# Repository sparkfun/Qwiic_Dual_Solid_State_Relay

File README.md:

SparkFun Qwiic Dual Solid State Relay
========================================

[*SparkFun Qwiic Dual Solid State Relay (COM-16810)*](https://www.sparkfun.com/products/16810)

The SparkFun Qwiic Dual Solid State Relay integrates two solid state relays on to a single board allowing you to control both of them from a microcontroller via I<sup>2</sup>C with the Qwiic Ecosystem. The relays are rated for 25A @240VAC so you can control some serious power with this board. 

The Qwiic Dual Solid State Relay comes fully assembled and uses the simple [Qwiic interface](https://www.sparkfun.com/qwiic). No soldering, no voltage translation, no figuring out which pin is SDA or SCL, just plug and go!

**Note:** Controlling high voltage (110/220VAC) requires certain precautions. A beginner can do it but if you're wary of working with high voltage, you may want to consider the pre-made [IoT Power Relay](https://www.sparkfun.com/products/14236). It's not controlled via I<sup>2</sup>C but the IoT Power Relay contains shielding to prevent accidental shock.

Repository Contents
-------------------

* **/Firmware** - Latest firmware
* **/Hardware** - Eagle design files (.brd, .sch)
* **/Production** - Production panel files (.brd)

Documentation
--------------
* **[SparkFun Qwiic Relay Arduino Library](https://github.com/sparkfun/SparkFun_Qwiic_Relay_Arduino_Library)** - Arduino library for SparkFun Qwiic Relay boards.
* **[SparkFun Qwiic Relay Python Package](https://github.com/sparkfun/Qwiic_Relay_Py)** - Python package for SparkFun Qwiic Solid State Relay boards.
* **[Hookup Guide](https://learn.sparkfun.com/tutorials/sparkfun-qwiic-dual-solid-state-relay-hookup-guide)** - Basic hookup guide for the Qwiic Dual Solid State Relay.
* **[SparkFun Fritzing repo](https://github.com/sparkfun/Fritzing_Parts)** - Fritzing diagrams for SparkFun products.
* **[SparkFun 3D Model repo](https://github.com/sparkfun/3D_Models)** - 3D models of SparkFun products. 

Product Versions
----------------
* [COM-16810](https://www.sparkfun.com/products/16810)- Initial release of the Qwiic Dual Solid State Relay.

License Information
-------------------

This product is _**open source**_! 

Please review the LICENSE.md file for license information. 

If you have any questions or concerns on licensing, please contact technical support on our [SparkFun forums](https://forum.sparkfun.com/viewforum.php?f=152).

Distributed as-is; no warranty is given.

- Your friends at SparkFun.

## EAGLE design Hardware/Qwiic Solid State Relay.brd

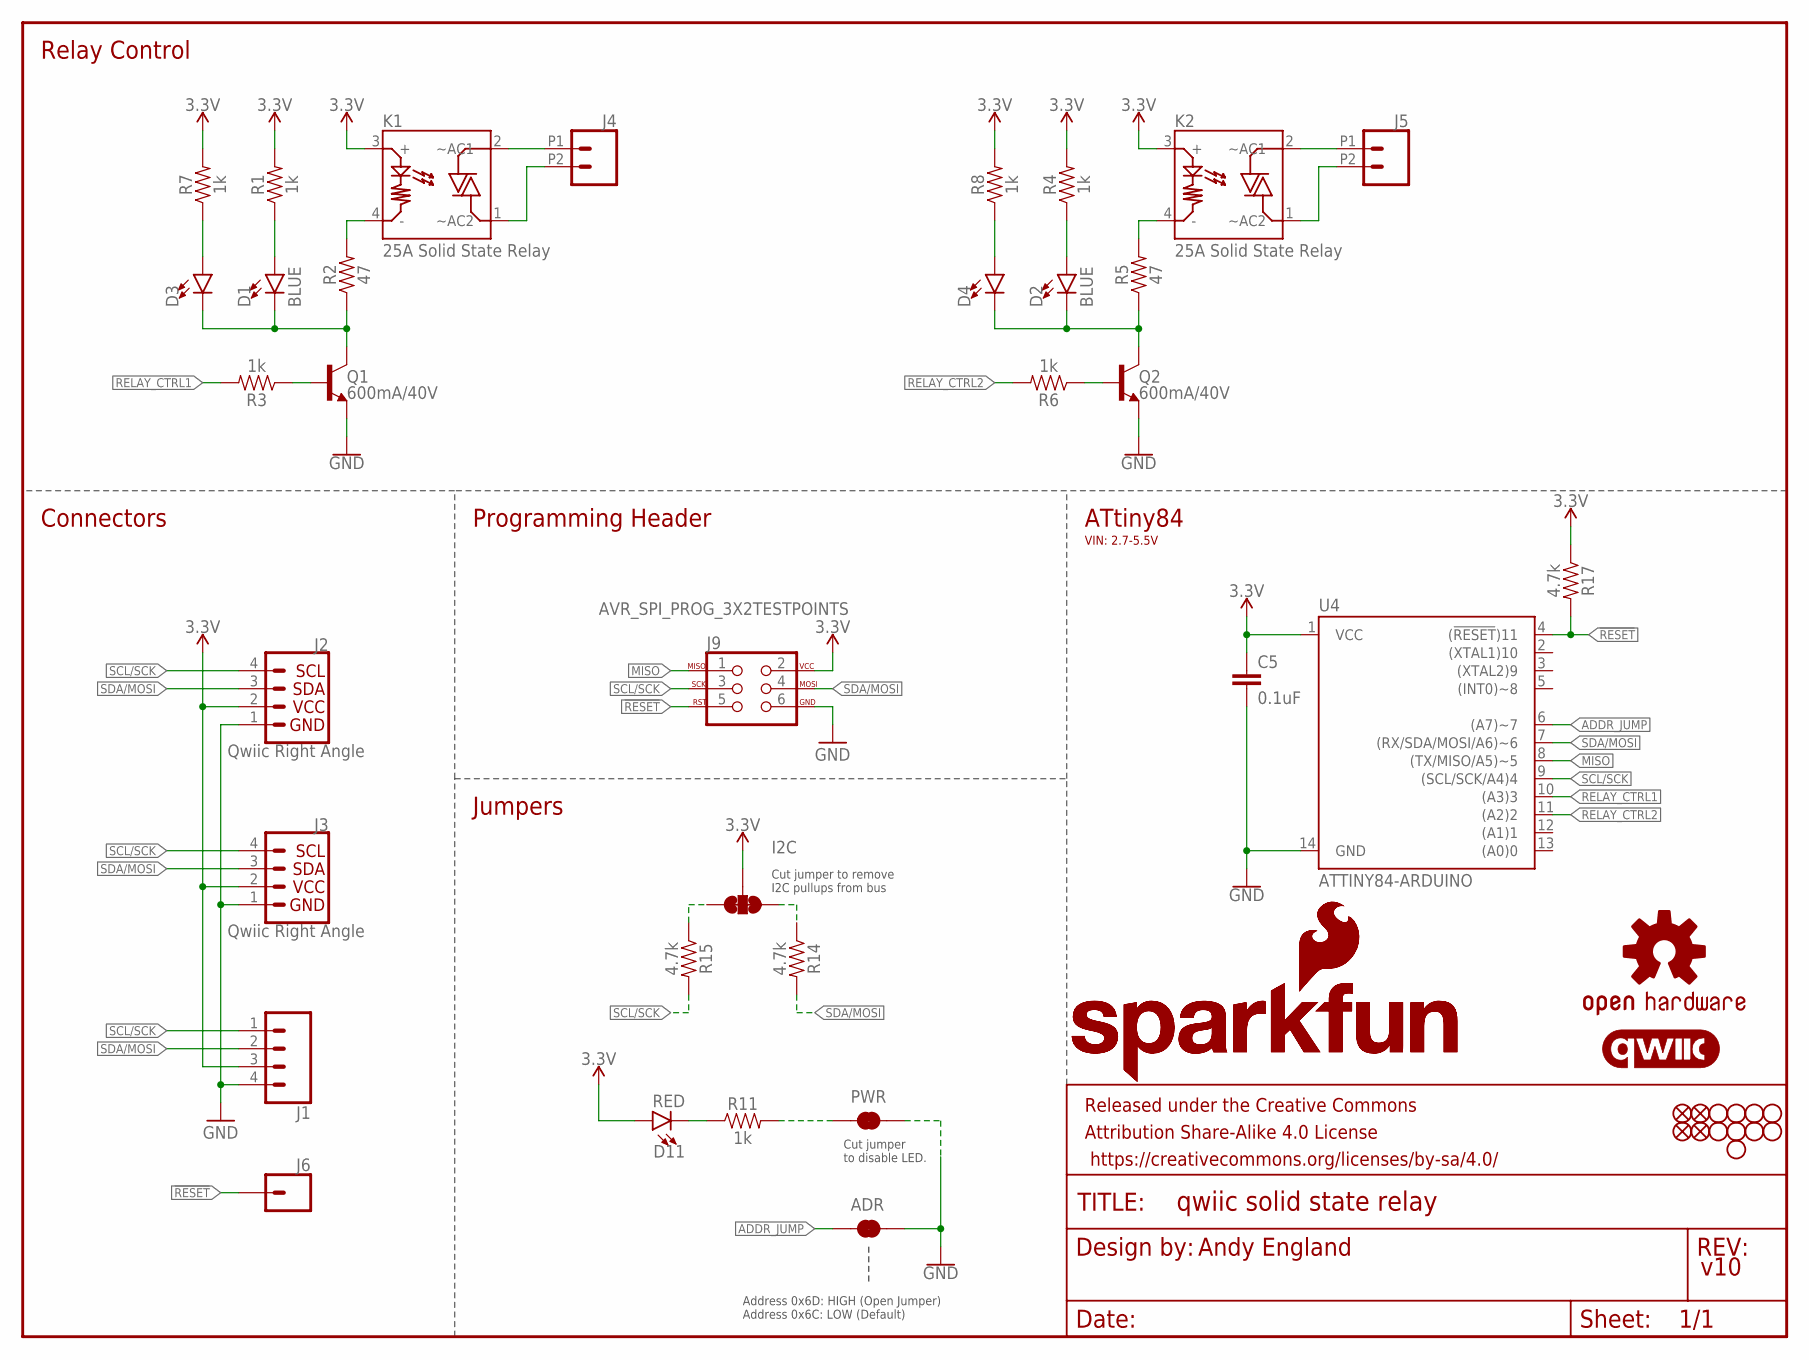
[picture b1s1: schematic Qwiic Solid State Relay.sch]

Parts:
ADR: JUMPER-SMT_2_NC_TRACE_SILK; SMT-JUMPER_2_NC_TRACE_SILK
C5: 0.1uF; 0603
D1, D2: BLUE; LED-0603
D3, D4: LED5MM; LED_5MM
D11: RED; LED-0603
FD1, FD2, FD3, FD4: FIDUCIAL1X2; FIDUCIAL-1X2
FRAME1: FRAME-LETTER; CREATIVE_COMMONS
I2C: JUMPER-SMT_3_2-NC_TRACE_SILK; SMT-JUMPER_3_2-NC_TRACE_SILK
J1: CONN_041X04_NO_SILK; 1X04_NO_SILK
J2, J3: Qwiic Right Angle; JST04_1MM_RA
J4, J5: CONN_02SCREWTERMINAL-6.35MM-2; 1X02_6.35_SCREWTERM
J6: CONN_01PTH_NO_SILK_YES_STOP; 1X01_NO_SILK
J9: AVR_SPI_PROG_3X2TESTPOINTS; 2X3_TEST_POINTS
JP1, JP2, JP3, JP4, JP5, JP6, JP7, JP8, JP10: STAND-OFF
K1, K2: 25A Solid State Relay; PTH_SOLIDSTATERELAY
LOGO1: SFE_LOGO_NAME_FLAME.2_INCH; SFE_LOGO_NAME_FLAME_.2
LOGO2: OSHW-LOGOS; OSHW-LOGO-S
LOGO3: SFE_LOGO_NAME_FLAME.3_INCH; SFE_LOGO_NAME_FLAME_.3
LOGO4: QWIIC_LOGO_5MM; QWIIC_5MM
PWR: JUMPER-SMT_2_NC_TRACE_SILK; SMT-JUMPER_2_NC_TRACE_SILK
Q1, Q2: 600mA/40V; SOT23-3
R1, R3, R4, R6, R7, R8, R11: 1k; 0603
R2, R5: 47; 0603
R14, R15, R17: 4.7k; 0603
U4: ATTINY84-ARDUINO; SO14

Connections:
3.3V: C5.1, D11.A, I2C.2, J1.3, J2.2, J3.2, J9.2, K1.3 (+), K2.3 (+), R1.2, R4.2, R7.2, R8.2, R17.1, U4.1 (VCC)
!RESET: J6.1, J9.5, R17.2, U4.4 ((!RESET!)11)
ADDR_JUMP: ADR.1, U4.6 ((A7)~7)
GND: ADR.2, C5.2, J1.4, J2.1, J3.1, J9.6, PWR.1, Q1.2 (E), Q2.2 (E), U4.14 (GND)
MISO: J9.1, U4.8 ((TX/MISO/A5)~5)
unnamed: K2.4 (-), R5.2
unnamed: D2.A, R4.1
unnamed: J4.P1 (2), K1.2 (~AC1)
unnamed: J4.P2 (1), K1.1 (~AC2)
unnamed: D1.A, R1.1
unnamed: J5.P1 (2), K2.2 (~AC1)
unnamed: J5.P2 (1), K2.1 (~AC2)
unnamed: K1.4 (-), R2.2
unnamed: D1.C, D3.K (C), Q1.3 (C), R2.1
unnamed: D3.A, R7.1
unnamed: D11.C, R11.1
unnamed: PWR.2, R11.2
unnamed: I2C.3, R15.1
unnamed: I2C.1, R14.1
unnamed: D2.C, D4.K (C), Q2.3 (C), R5.1
unnamed: D4.A, R8.1
OPTO_1: Q1.1 (B), R3.1
OPTO_2: Q2.1 (B), R6.1
RELAY_CTRL1: R3.2, U4.10 ((A3)3)
RELAY_CTRL2: R6.2, U4.11 ((A2)2)
SCL/SCK: J1.1, J2.4, J3.4, J9.3, R15.2, U4.9 ((SCL/SCK/A4)4)
SDA/MOSI: J1.2, J2.3, J3.3, J9.4, R14.2, U4.7 ((RX/SDA/MOSI/A6)~6)

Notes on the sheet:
Andy England
v10
Connectors
ATtiny84
Programming Header
Address 0x6D: HIGH (Open Jumper) Address 0x6C: LOW (Default)
Cut jumper to disable LED.
Jumpers
Relay Control
Cut jumper to remove I2C pullups from bus
VIN: 2.7-5.5V

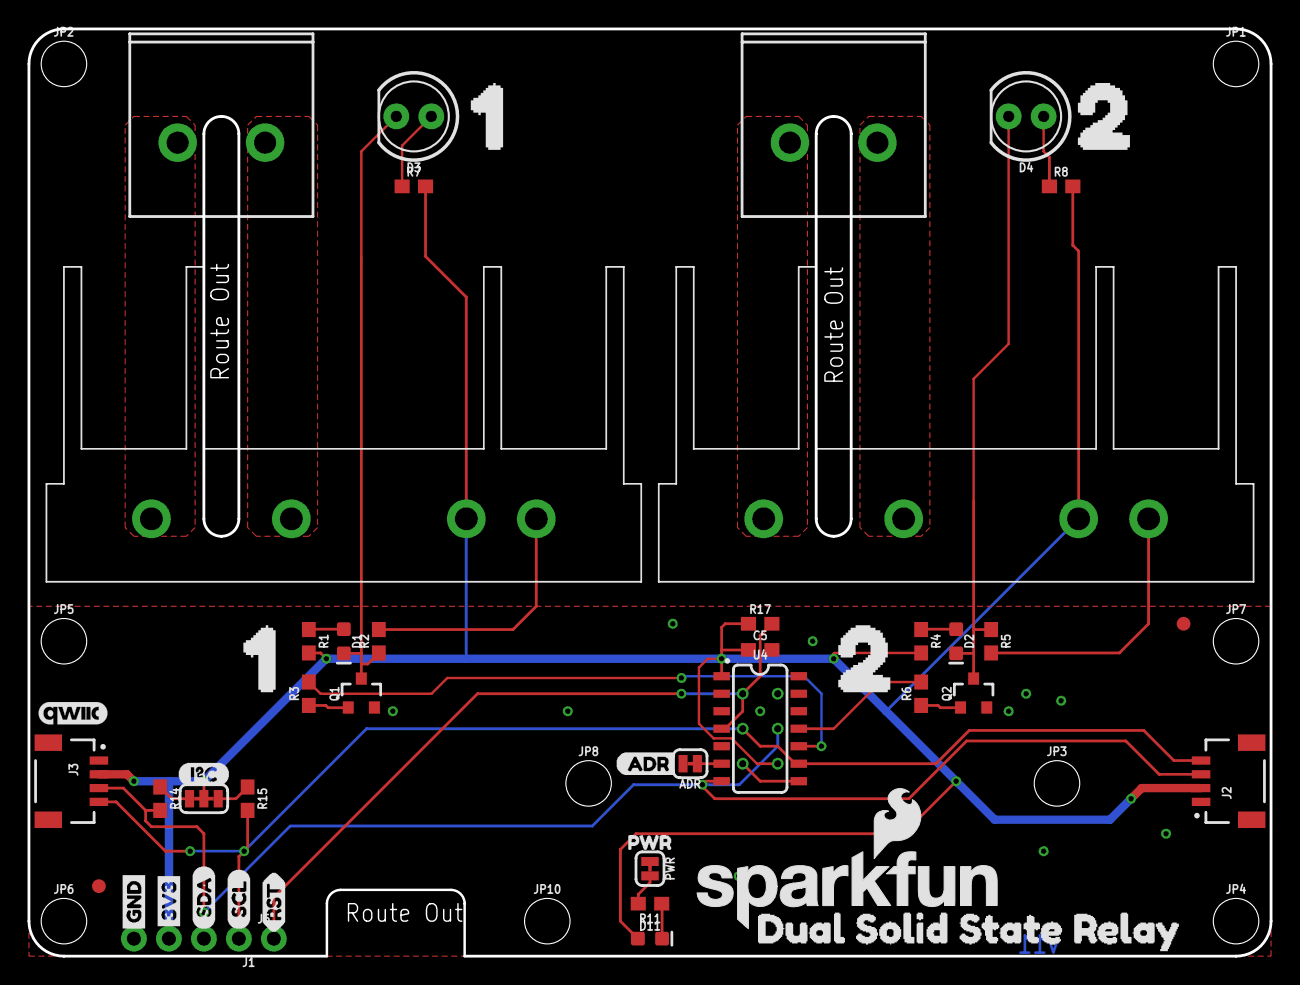
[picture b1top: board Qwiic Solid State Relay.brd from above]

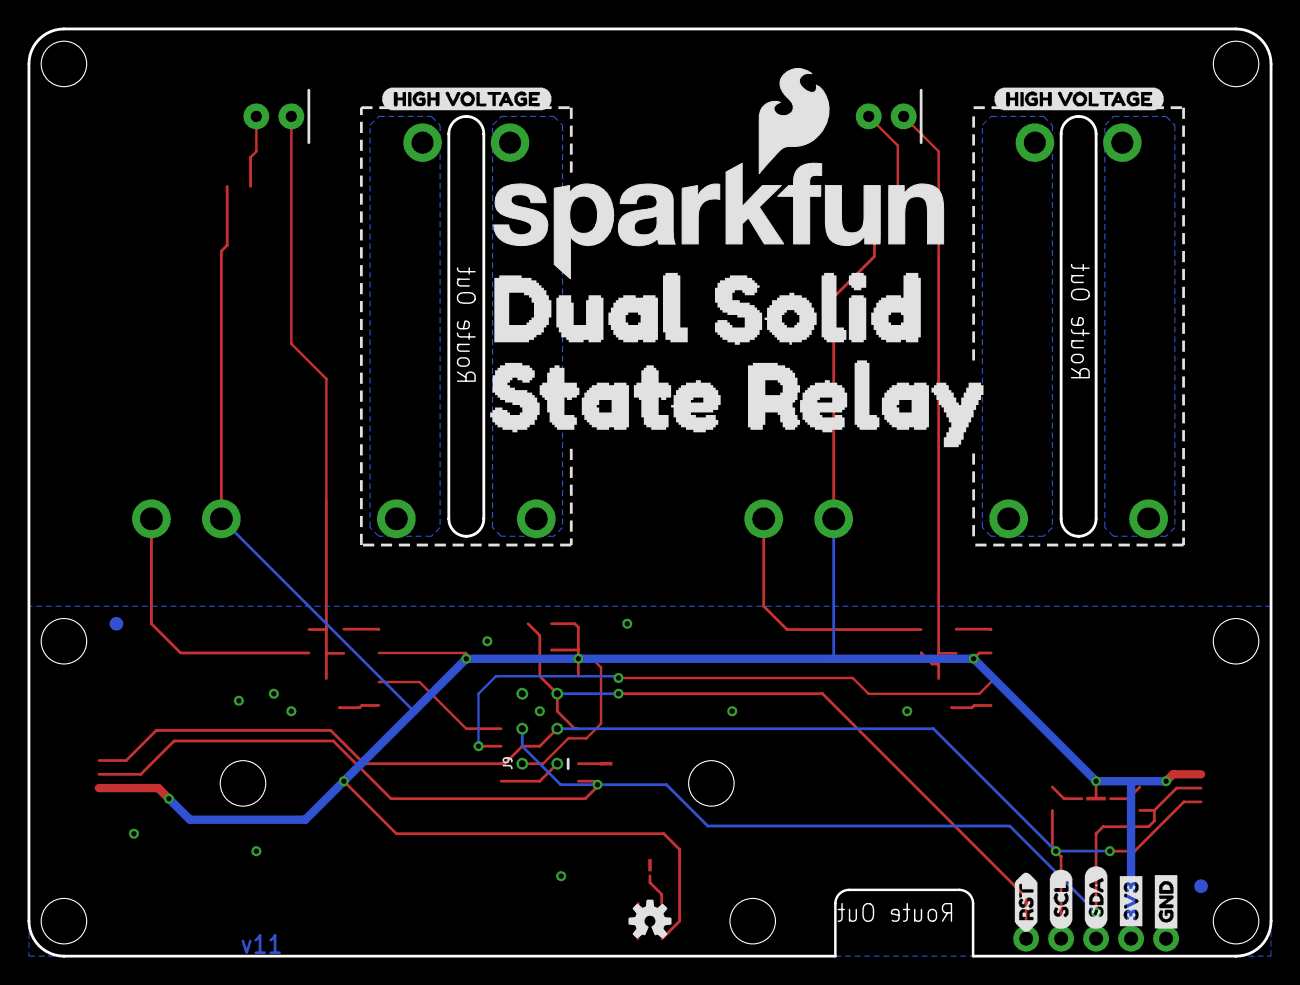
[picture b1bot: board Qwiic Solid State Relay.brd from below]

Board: 2 copper layers, 90.2 x 67.3 mm, 73 parts (14 on the bottom side), 27 nets.

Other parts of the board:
U$1: DUAL_SOLID_STATE_RELAY0
U$2: DUAL_SOLID0
U$3: STATE_RELAY1
U$5, U$9: 11
U$6, U$10: 22
U$7, U$8: HIGH_VOLTAGE0
U$11, U$12: RST_I
U$13, U$14: GND_P
U$15: I2C
U$16, U$17: 3V3_P
U$18, U$19: SCL_IO
U$20, U$21: SDA_IO
U$23: ADR3
U$24: PWR_TO

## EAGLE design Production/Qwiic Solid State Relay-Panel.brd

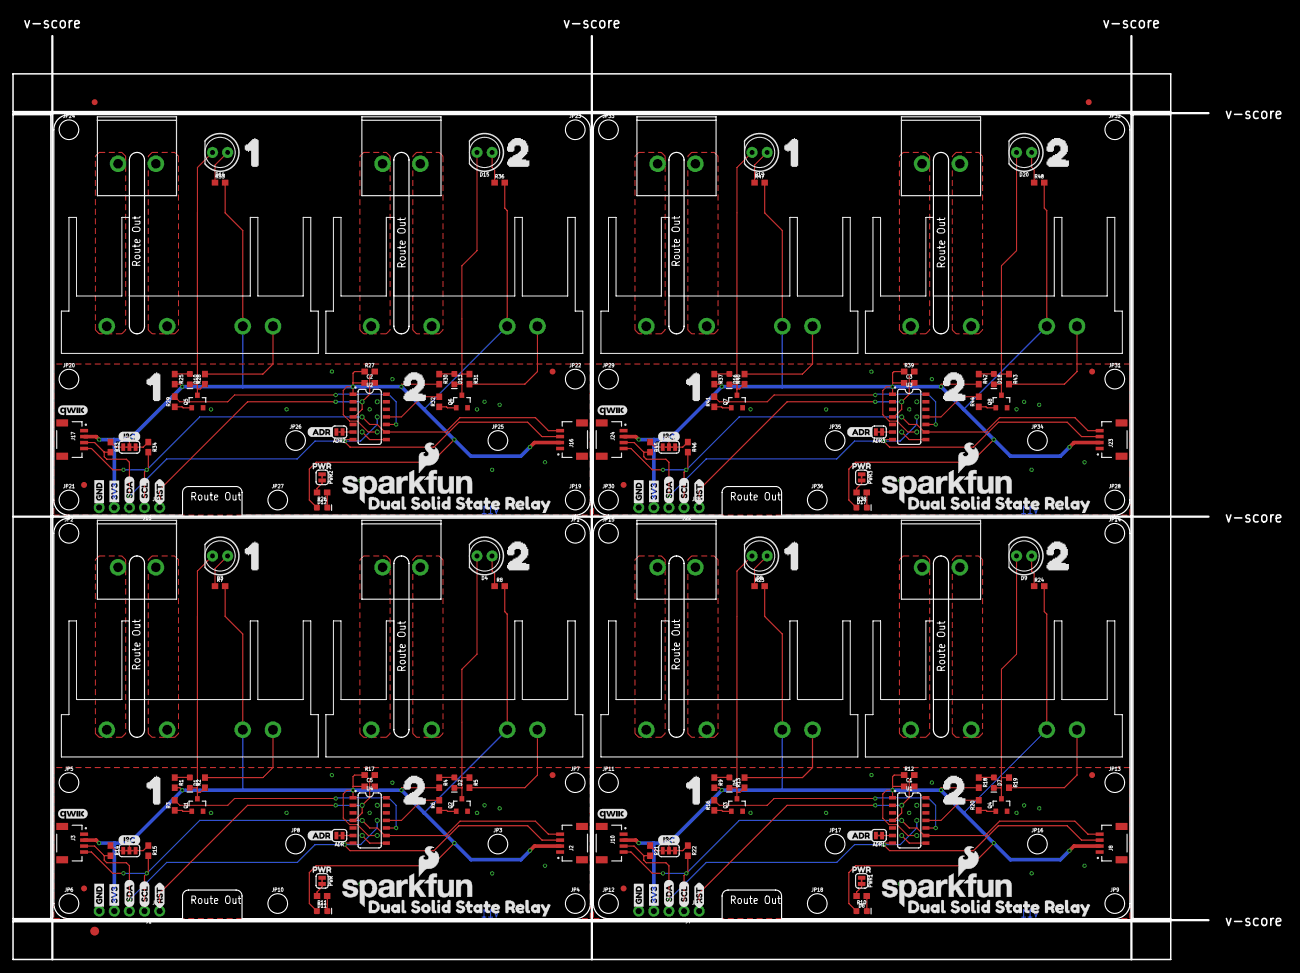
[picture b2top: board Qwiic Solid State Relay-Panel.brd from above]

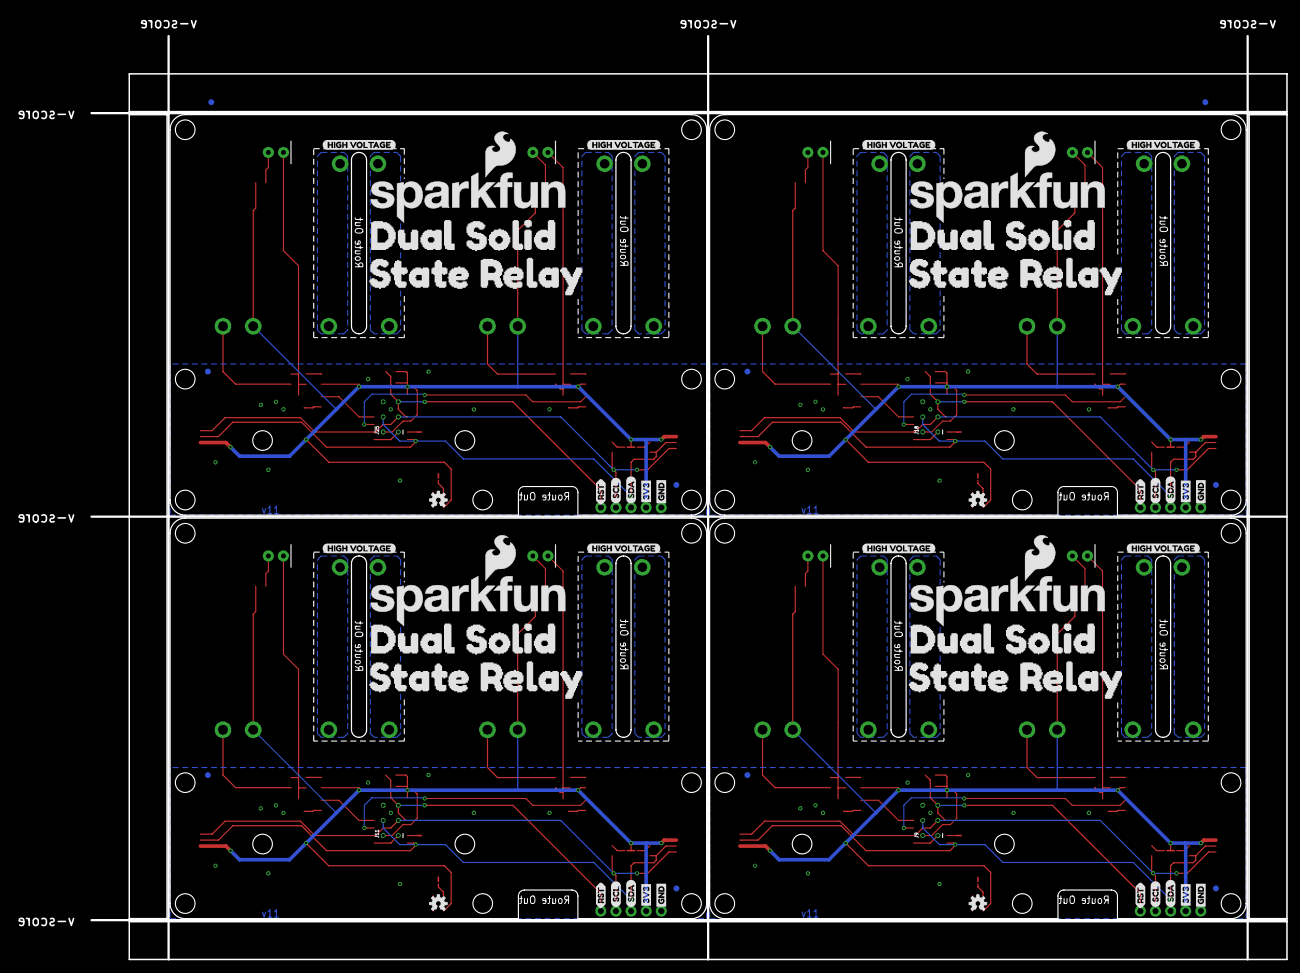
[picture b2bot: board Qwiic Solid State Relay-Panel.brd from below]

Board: 2 copper layers, 214.1 x 159.1 mm, 293 parts (58 on the bottom side), 108 nets.

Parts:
ADR, ADR1, ADR2, ADR3: JUMPER-SMT_2_NC_TRACE_SILK; SMT-JUMPER_2_NC_TRACE_SILK
C1, C2, C3, C5: 0.1uF; 0603
D1, D2, D5, D7, D10, D13, D16, D18: BLUE; LED-0603
D3, D4, D8, D9, D14, D15, D19, D20: LED_5MM
D6, D11, D12, D17: RED; LED-0603
E$1, E$2, E$3, E$4: FIDUCIAL-1X2
E$5: FIDUCIAL-1.5X3
FD1, FD2, FD3, FD4, FD5, FD6, FD7, FD8, FD9, FD10, FD11, FD12, FD13, FD14, FD15, FD16: FIDUCIAL1X2; FIDUCIAL-1X2
I2C, I2C1, I2C2, I2C3: JUMPER-SMT_3_2-NC_TRACE_SILK; SMT-JUMPER_3_2-NC_TRACE_SILK
J1, J7, J15, J22: 1X04_NO_SILK
J2, J3, J8, J10, J16, J17, J23, J24: Qwiic Right Angle; JST04_1MM_RA
J4, J5, J12, J13, J19, J20, J26, J27: 1X02_6.35_SCREWTERM
J6, J14, J21, J28: 1X01_NO_SILK
J9, J11, J18, J25: AVR_SPI_PROG_3X2TESTPOINTS; 2X3_TEST_POINTS
JP1, JP2, JP3, JP4, JP5, JP6, JP7, JP8, JP9, JP10, JP11, JP12, JP13, JP14, JP15, JP16, JP17, JP18, JP19, JP20, JP21, JP22, JP23, JP24, JP25, JP26, JP27, JP28, JP29, JP30, JP31, JP32, JP33, JP34, JP35, JP36: STAND-OFF
K1, K2, K3, K4, K5, K6, K7, K8: 25A Solid State Relay; PTH_SOLIDSTATERELAY
LOGO1, LOGO6, LOGO10, LOGO14: SFE_LOGO_NAME_FLAME.2_INCH; SFE_LOGO_NAME_FLAME_.2
LOGO2, LOGO5, LOGO9, LOGO13: OSHW-LOGOS; OSHW-LOGO-S
LOGO3, LOGO7, LOGO11, LOGO15: SFE_LOGO_NAME_FLAME.3_INCH; SFE_LOGO_NAME_FLAME_.3
LOGO4, LOGO8, LOGO12, LOGO16: QWIIC_LOGO_5MM; QWIIC_5MM
PWR, PWR1, PWR2, PWR3: JUMPER-SMT_2_NC_TRACE_SILK; SMT-JUMPER_2_NC_TRACE_SILK
Q1, Q2, Q3, Q4, Q5, Q6, Q7, Q8: 600mA/40V; SOT23-3
R1, R3, R4, R6, R7, R8, R9, R10, R11, R16, R18, R20, R23, R24, R25, R26, R29, R30, R32, R35, R36, R37, R38, R41, R42, R44, R47, R48: 1k; 0603
R2, R5, R13, R19, R28, R31, R40, R43: 47; 0603
R12, R14, R15, R17, R21, R22, R27, R33, R34, R39, R45, R46: 4.7k; 0603
U1, U2, U3, U4: ATTINY84-ARDUINO; SO14
U$1, U$44, U$66, U$88: DUAL_SOLID_STATE_RELAY0
U$2, U$38, U$60, U$82: DUAL_SOLID0
U$3, U$39, U$61, U$83: STATE_RELAY1
U$4, U$5, U$9, U$25, U$45, U$47, U$67, U$69: 11
U$6, U$10, U$22, U$26, U$46, U$48, U$68, U$70: 22
U$7, U$8, U$40, U$41, U$62, U$63, U$84, U$85: HIGH_VOLTAGE0
U$11, U$12, U$42, U$43, U$64, U$65, U$86, U$87: RST_I
U$13, U$14, U$27, U$28, U$49, U$50, U$71, U$72: GND_P
U$15, U$29, U$51, U$73: I2C
U$16, U$17, U$30, U$31, U$52, U$53, U$74, U$75: 3V3_P
U$18, U$19, U$32, U$33, U$54, U$55, U$76, U$77: SCL_IO
U$20, U$21, U$34, U$35, U$56, U$57, U$78, U$79: SDA_IO
U$23, U$36, U$58, U$80: ADR3
U$24, U$37, U$59, U$81: PWR_TO

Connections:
3.3V: C5.1, D11.A, I2C.2, J1.3, J2.2, J3.2, J9.2, K1.3, K2.3, R1.2, R4.2, R7.2, R8.2, R17.1, U4.1
3.3V1: C1.1, D6.A, I2C1.2, J7.3, J8.2, J10.2, J11.2, K3.3, K4.3, R9.2, R12.1, R18.2, R23.2, R24.2, U1.1
3.3V2: C2.1, D12.A, I2C2.2, J15.3, J16.2, J17.2, J18.2, K5.3, K6.3, R25.2, R27.1, R30.2, R35.2, R36.2, U2.1
3.3V3: C3.1, D17.A, I2C3.2, J22.3, J23.2, J24.2, J25.2, K7.3, K8.3, R37.2, R39.1, R42.2, R47.2, R48.2, U3.1
!RESET: J6.1, J9.5, R17.2, U4.4
!RESET1: J11.5, J14.1, R12.2, U1.4
!RESET2: J18.5, J21.1, R27.2, U2.4
!RESET3: J25.5, J28.1, R39.2, U3.4
ADDR_JUMP: ADR.1, U4.6
ADDR_JUMP1: ADR1.1, U1.6
ADDR_JUMP2: ADR2.1, U2.6
ADDR_JUMP3: ADR3.1, U3.6
GND: ADR.2, C5.2, J1.4, J2.1, J3.1, J9.6, PWR.1, Q1.2, Q2.2, U4.14
GND1: ADR1.2, C1.2, J7.4, J8.1, J10.1, J11.6, PWR1.1, Q3.2, Q4.2, U1.14
GND2: ADR2.2, C2.2, J15.4, J16.1, J17.1, J18.6, PWR2.1, Q5.2, Q6.2, U2.14
GND3: ADR3.2, C3.2, J22.4, J23.1, J24.1, J25.6, PWR3.1, Q7.2, Q8.2, U3.14
MISO: J9.1, U4.8
MISO1: J11.1, U1.8
MISO2: J18.1, U2.8
MISO3: J25.1, U3.8
unnamed: D6.C, R10.1
unnamed: PWR1.2, R10.2
unnamed: K2.4, R5.2
unnamed: D2.A, R4.1
unnamed: J4.P1, K1.2
unnamed: J4.P2, K1.1
unnamed: D1.A, R1.1
unnamed: J5.P1, K2.2
unnamed: J5.P2, K2.1
unnamed: K1.4, R2.2
unnamed: D1.C, D3.K, Q1.3, R2.1
unnamed: D3.A, R7.1
unnamed: D11.C, R11.1
unnamed: PWR.2, R11.2
unnamed: I2C.3, R15.1
unnamed: I2C.1, R14.1
unnamed: D2.C, D4.K, Q2.3, R5.1
unnamed: D4.A, R8.1
unnamed: K3.4, R13.2
unnamed: D5.A, R9.1
unnamed: K4.4, R19.2
unnamed: D7.A, R18.1
unnamed: I2C1.3, R22.1
unnamed: I2C1.1, R21.1
unnamed: J12.P1, K3.2
unnamed: J12.P2, K3.1
unnamed: J13.P1, K4.2
unnamed: J13.P2, K4.1
unnamed: D5.C, D8.K, Q3.3, R13.1
unnamed: D8.A, R23.1
unnamed: D7.C, D9.K, Q4.3, R19.1
unnamed: D9.A, R24.1
unnamed: D12.C, R26.1
unnamed: PWR2.2, R26.2
unnamed: K5.4, R28.2
unnamed: D10.A, R25.1
unnamed: K6.4, R31.2
unnamed: D13.A, R30.1
unnamed: I2C2.3, R34.1
unnamed: I2C2.1, R33.1
unnamed: J19.P1, K5.2
unnamed: J19.P2, K5.1
unnamed: J20.P1, K6.2
unnamed: J20.P2, K6.1
unnamed: D10.C, D14.K, Q5.3, R28.1
unnamed: D14.A, R35.1
unnamed: D13.C, D15.K, Q6.3, R31.1
unnamed: D15.A, R36.1
unnamed: D17.C, R38.1
unnamed: PWR3.2, R38.2
unnamed: K7.4, R40.2
unnamed: D16.A, R37.1
unnamed: K8.4, R43.2
unnamed: D18.A, R42.1
unnamed: I2C3.3, R46.1
unnamed: I2C3.1, R45.1
unnamed: J26.P1, K7.2
unnamed: J26.P2, K7.1
unnamed: J27.P1, K8.2
unnamed: J27.P2, K8.1
unnamed: D16.C, D19.K, Q7.3, R40.1
unnamed: D19.A, R47.1
unnamed: D18.C, D20.K, Q8.3, R43.1
unnamed: D20.A, R48.1
OPTO_1: Q1.1, R3.1
OPTO_2: Q2.1, R6.1
OPTO_3: Q3.1, R16.1
OPTO_4: Q4.1, R20.1
OPTO_5: Q5.1, R29.1
OPTO_6: Q6.1, R32.1
OPTO_7: Q7.1, R41.1
OPTO_8: Q8.1, R44.1
RELAY_CTRL1: R3.2, U4.10
RELAY_CTRL2: R6.2, U4.11
RELAY_CTRL3: R16.2, U1.10
RELAY_CTRL4: R20.2, U1.11
RELAY_CTRL5: R29.2, U2.10
RELAY_CTRL6: R32.2, U2.11
RELAY_CTRL7: R41.2, U3.10
RELAY_CTRL8: R44.2, U3.11
SCL/SCK: J1.1, J2.4, J3.4, J9.3, R15.2, U4.9
SCL/SCK1: J7.1, J8.4, J10.4, J11.3, R22.2, U1.9
SCL/SCK2: J15.1, J16.4, J17.4, J18.3, R34.2, U2.9
SCL/SCK3: J22.1, J23.4, J24.4, J25.3, R46.2, U3.9
SDA/MOSI: J1.2, J2.3, J3.3, J9.4, R14.2, U4.7
SDA/MOSI1: J7.2, J8.3, J10.3, J11.4, R21.2, U1.7
SDA/MOSI2: J15.2, J16.3, J17.3, J18.4, R33.2, U2.7
SDA/MOSI3: J22.2, J23.3, J24.3, J25.4, R45.2, U3.7

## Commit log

2020-05-27 pre-design review
2020-05-27 post review/checklist changes
2020-05-27 removing overlap errors
2020-05-29 adding panel
2020-07-07 Updating Readme
    Updating readme with proper links. Product photo still needed.
2020-08-21 flipping relay footprint
2020-09-02 updating to new panel
2020-09-17 updating address note
2020-09-18 changing pins on firmware
2020-09-18 Update README
    Adding product photo and Python package link.
2020-09-21 updating slowPWM function
2020-09-24 Release Update
    Removing Documentation folder and updating Readme to reflect that.
2021-12-23 This is a Klipper version.
    This version works with Klipper.
2021-12-23 Update qwiic_dual_ssr_relay.py
    Updates to fix some things.

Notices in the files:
parts and their libraries:
SparkFun-Capacitors: Licensing: Creative Commons ShareAlike 4.0 International - https://creativecommons.org/licenses/by-sa/4.0
SparkFun-Aesthetics: Released under the Creative Commons Attribution Share-Alike 4.0 License
SparkFun-Aesthetics: https://creativecommons.org/licenses/by-sa/4.0
